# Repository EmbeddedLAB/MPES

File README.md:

# REPOSITÓRIO DA PLACA MPES (Multi Purpose Embedded Shield)

Projeto desenvolvido no laboratório de Sistemas Embarcados do Instituto Federal de São Paulo.

Para mais informações, acesse a nossa página no Facebook:

https://www.facebook.com/embedded.lab.ifsp/

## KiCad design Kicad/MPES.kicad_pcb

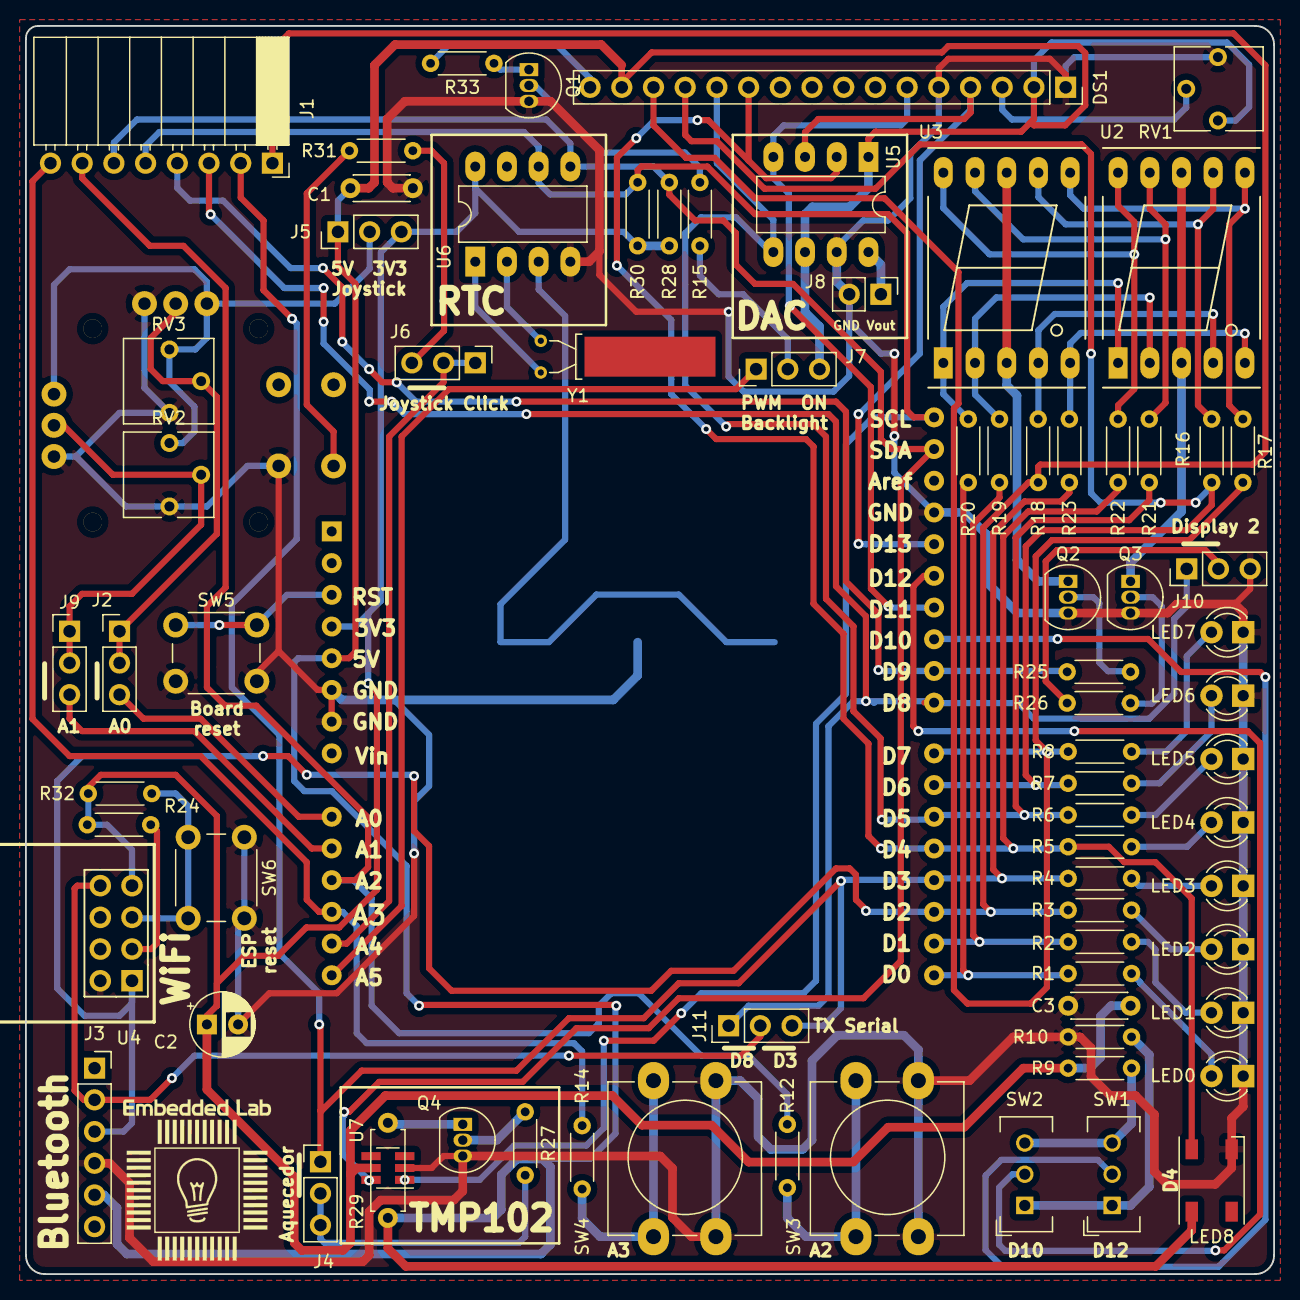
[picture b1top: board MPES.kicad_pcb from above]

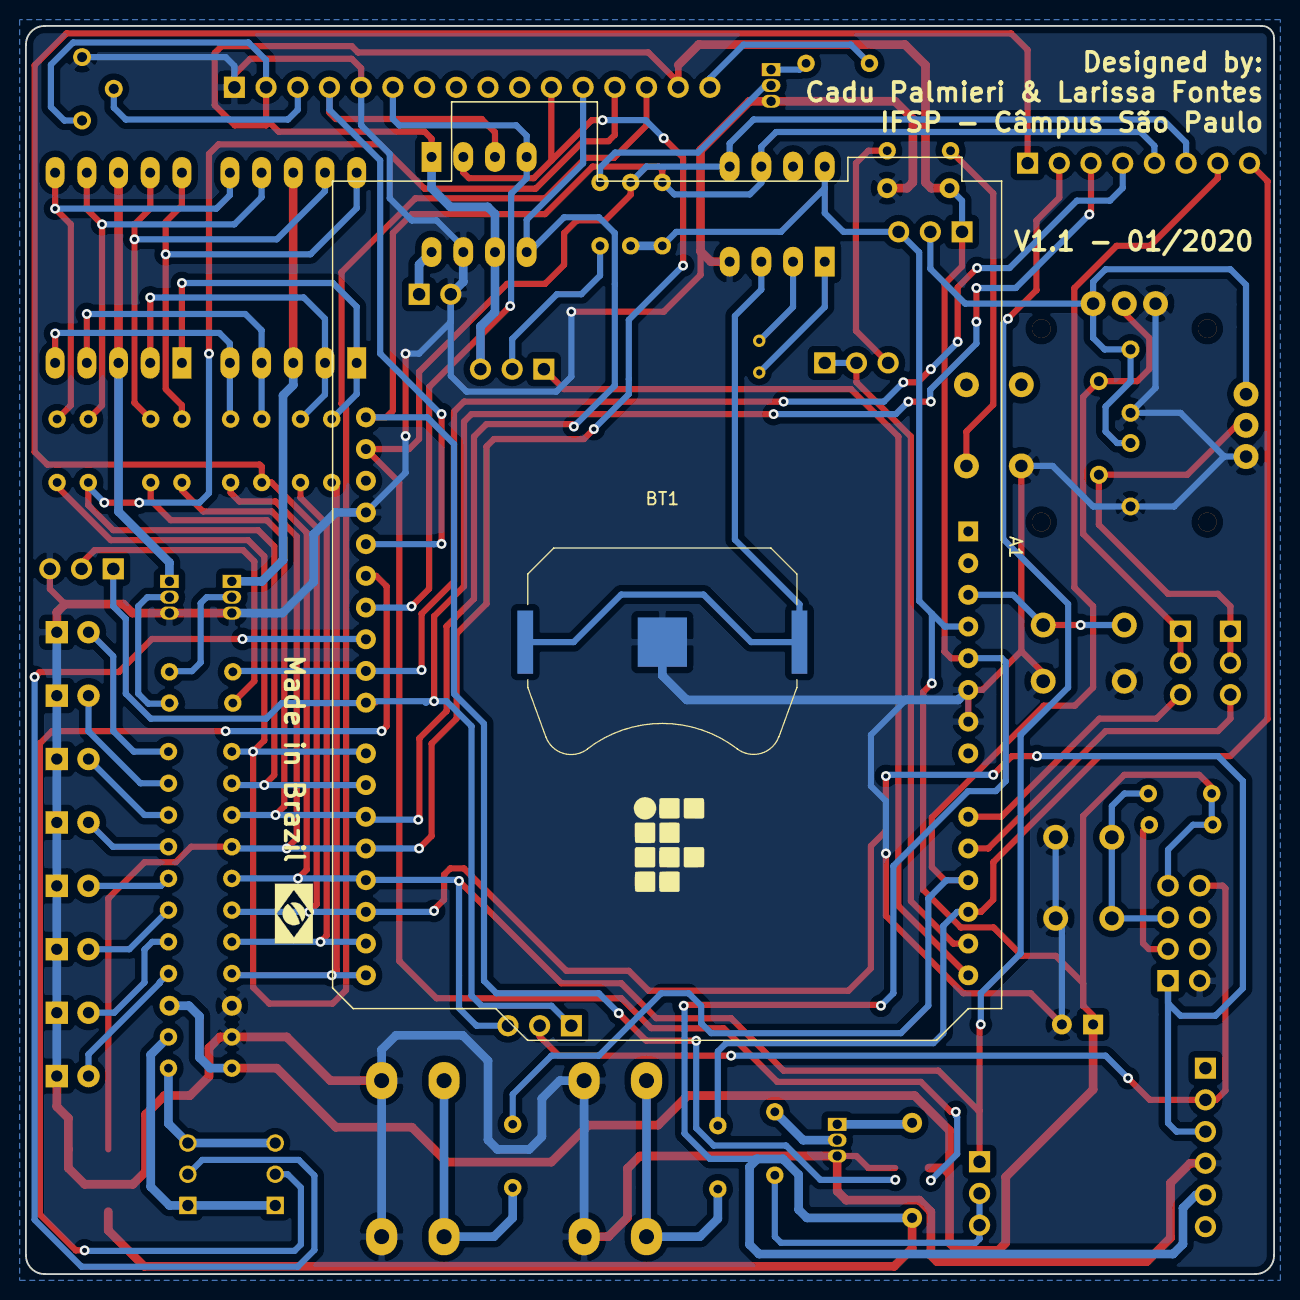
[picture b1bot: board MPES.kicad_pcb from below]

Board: 2 copper layers, 100.0 x 100.0 mm, 78 parts (2 on the bottom side), 71 nets.

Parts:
A1: Arduino_UNO_R3
BT1: Battery_Cell; Keystone_3034_1x20mm-CoinCell
C1, C3: C; C_Disc_D4.3mm_W1.9mm_P5.00mm
C2: CP; CP_Radial_D5.0mm_P2.50mm
DS1: WC1602A; PinSocket_1x16_P2.54mm_Vertical
J1: Conn_01x08; PinSocket_1x08_P2.54mm_Horizontal
J2: Conn_01x03; Pin_Header_Straight_1x03_Pitch2.54mm
J3: Conn_01x06; PinSocket_1x06_P2.54mm_Vertical
J4, J5, J6, J7, J9, J10, J11: Conn_01x03; PinHeader_1x03_P2.54mm_Vertical
J8: Conn_01x02; PinHeader_1x02_P2.54mm_Vertical
LED0, LED1, LED2, LED3, LED4, LED5, LED6, LED7: LED; LED_D3.0mm
LED8: WS2812B; LED_WS2812B-PLCC4
Q1, Q2, Q3, Q4: BC548; TO-92_Inline
R1, R2, R3, R4, R5, R6, R7, R8, R9, R10, R12, R14, R15, R16, R17, R18, R19, R20, R21, R22, R23, R24, R25, R26, R27, R28, R30, R31, R32, R33: R; R_Axial_DIN0204_L3.6mm_D1.6mm_P5.08mm_Horizontal
R29: R; R_Axial_DIN0207_L6.3mm_D2.5mm_P7.62mm_Horizontal
RV1: R_POT_TRIM; Potentiometer_Trimmer_Vishay_T73YP_Horizontal
RV2, RV3: R_POT_TRIM; Potentiometer_Vishay_T73YP_Vertical
SW1, SW2: SW_SPDT; chavinha3pos
SW3, SW4: SW_Push; SW_PUSH-12mm_Wuerth-430476085716
SW5, SW6: SW_Push; SW_PUSH_6mm
U1: JOYSTICK_BUTTON; Joystick_Button
U2, U3: KCSC02-107; 7SegmentLED_LTS6760_LTS6780
U4: ESP-01v090; esp01
U5: MCP4921-EP; DIP-8_W7.62mm_LongPads
U6: DS1307+; DIP-8_W7.62mm_LongPads
U7: TMP102; SOT-23-6_Handsoldering
Y1: Crystal; Crystal_AT310_D3.0mm_L10.0mm_Horizontal_1EP_style1

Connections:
+3V3: A1.4, C2.1, C3.1, J5.3, R9.1, R24.2, R28.1, R30.1, R32.1, U4.7, U6.8, U7.5
+5V: A1.5, C1.1, DS1.2, DS1.15, J3.5, J5.1, J7.3, LED8.1, R29.1, RV1.3, U5.1, U5.6
A0: J2.1, J2.2, RV3.2, U1.X2
A0_j: A1.9, J2.3
A1: J9.1, J9.2, RV2.2, U1.Y2
A1_j: A1.10, J9.3
A2: A1.11, J1.7, R12.1
A3: A1.12, J1.8, R14.1
A4: A1.13, J6.1, J6.2
A5: A1.14, J7.1
D0: A1.15, R1.1, R20.2
D1: A1.16, R2.1, R19.2
D2: A1.17, J1.1, J3.3, R3.1, R18.2, U4.1
D3: A1.18, J1.2, J4.1, J11.3, R4.1, R23.2
D4: A1.19, DS1.11, LED8.4, R5.1, R22.2, U5.2
D5: A1.20, DS1.12, R6.1, R21.2, U5.5
D6: A1.21, DS1.13, R7.1, R16.2
D7: A1.22, DS1.14, R8.1, R17.2
D8: A1.23, J1.3, J10.1, J11.1
D9: A1.24, J1.4, R25.2
D10: A1.25, SW1.2
D11: A1.26, DS1.6, U5.4
D12: A1.27, SW2.2
D13: A1.28, DS1.4, U5.3
GND: A1.6, A1.7, A1.29, BT1.2, C1.2, C2.2, C3.2, DS1.1, DS1.5, J3.4, J8.2, J10.3, LED0.1, LED1.1, LED2.1, LED3.1, LED4.1, LED5.1, LED6.1, LED7.1, LED8.3, Q1.3, Q2.3, Q3.3, Q4.3, R10.1, RV1.1, RV2.1, RV3.1, SW3.2, SW4.2, SW5.2, SW6.1, U1.SW1, U1.X1, U1.Y1, U4.2, U5.7, U6.4, U7.2
unnamed: BT1.1, U6.3
unnamed: LED0.2, R1.2
unnamed: LED1.2, R2.2
unnamed: LED2.2, R3.2
unnamed: LED3.2, R4.2
unnamed: LED4.2, R5.2
unnamed: LED5.2, R6.2
unnamed: LED6.2, R7.2
unnamed: LED7.2, R8.2
unnamed: DS1.3, RV1.2
unnamed: DS1.16, R33.2
unnamed: J4.2, J4.3, R27.2
unnamed: J5.2, RV2.3, RV3.3, U1.X3, U1.Y3
unnamed: J6.3, R31.1
unnamed: J7.2, R15.2
unnamed: J8.1, U5.8
unnamed: J10.2, R26.2
unnamed: Q1.1, R33.1
unnamed: Q1.2, R15.1
unnamed: Q2.1, U3.3, U3.8
unnamed: Q2.2, R25.1
unnamed: Q3.1, U2.3, U2.8
unnamed: Q3.2, R26.1
unnamed: Q4.1, R29.2
unnamed: Q4.2, R27.1
unnamed: R9.2, SW1.3, SW2.3
unnamed: R10.2, SW1.1, SW2.1
unnamed: R12.2, SW3.1
unnamed: R14.2, SW4.1
unnamed: R16.1, U2.7, U3.7
unnamed: R17.1, U2.6, U3.6
unnamed: R18.1, U2.4, U3.4
unnamed: R19.1, U2.2, U3.2
unnamed: R20.1, U2.1, U3.1
unnamed: R21.1, U2.9, U3.9
unnamed: R22.1, U2.10, U3.10
unnamed: R23.1, U2.5, U3.5
unnamed: R24.1, U4.3
unnamed: R31.2, U1.SW2
unnamed: U6.1, Y1.1
unnamed: U6.2, Y1.2
SCL: A1.32, J1.5, R30.2, U6.6, U7.1
SDA: A1.31, J1.6, R28.2, U6.5, U7.6
rst: A1.3, SW5.1
rst1: R32.2, SW6.2, U4.5
tx1: J3.2, J11.2, U4.8

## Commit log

2020-03-05 Create LICENSE
